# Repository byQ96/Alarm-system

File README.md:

# Alarm-system
Alarm system made under arduino platform

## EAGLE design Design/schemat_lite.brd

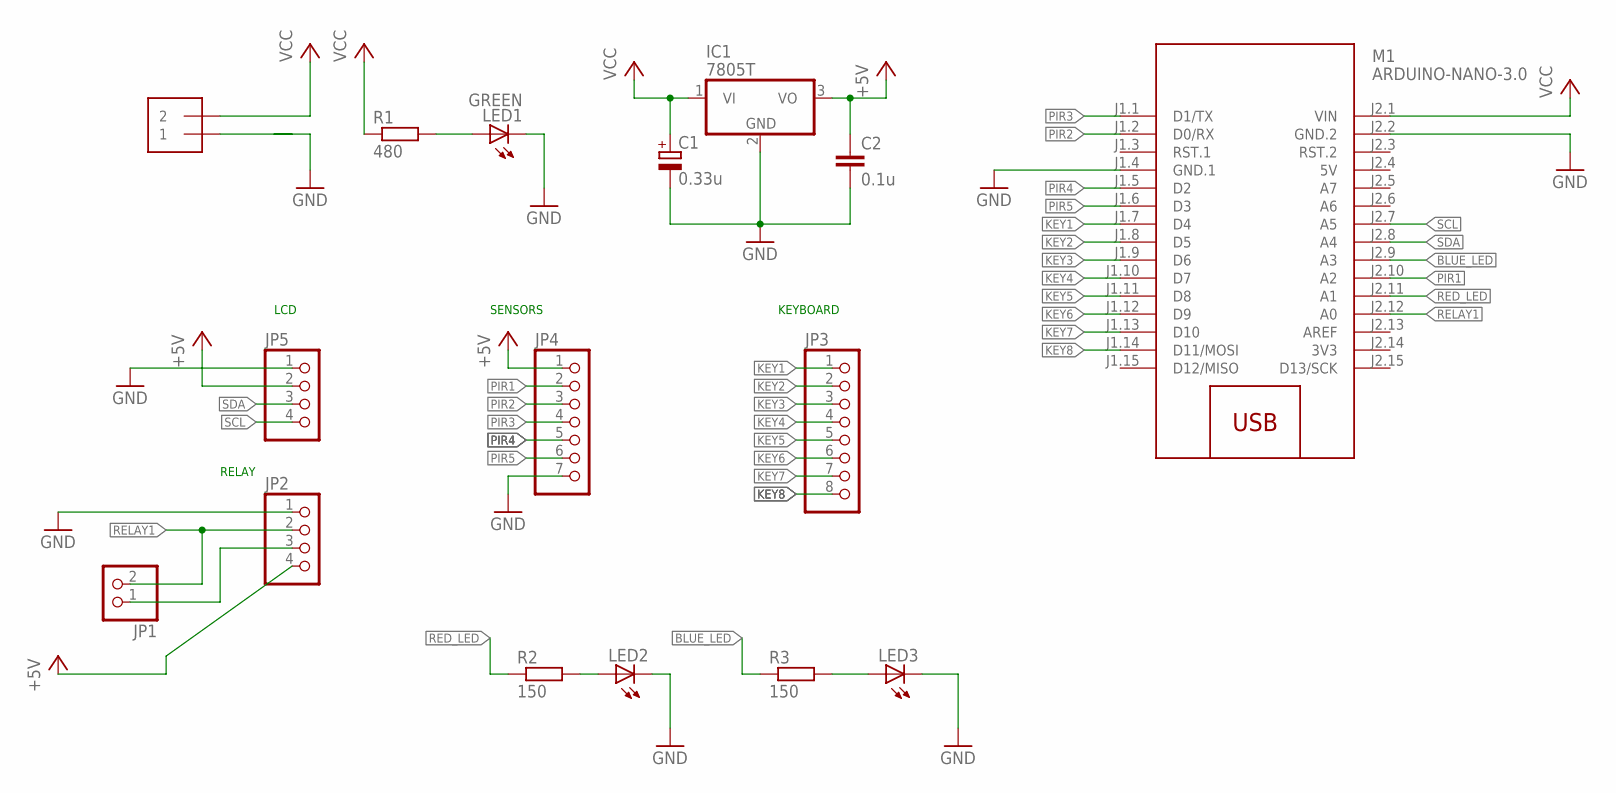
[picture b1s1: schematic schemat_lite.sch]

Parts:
C1: 0.33u; E5-4
C2: 0.1u; C050-025X075
IC1: 7805T; TO220H
J1: 1X2-3.5MM
JP1: PINHD-1X2; 1X02
JP2, JP5: PINHD-1X4; 1X04
JP3: PINHD-1X8; 1X08
JP4: PINHD-1X7; 1X07
LED1: GREEN; LED5MM
LED2, LED3: LED5MM
M1: ARDUINO-NANO-3.0
R1: 480; 0204/7
R2, R3: 150; 0204/7

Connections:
3V3: M1.J2.14 (3V3)
5V: M1.J2.4 (5V)
+5V: C2.1, IC1.3 (VO), JP2.4, JP4.1, JP5.2
BLUE_LED: M1.J2.9 (A3), R3.1
GND: C1.-, C2.2, IC1.2 (GND), J1.1, JP2.1, JP4.7, JP5.1, LED1.K (C), LED2.K (C), LED3.K (C), M1.J1.4 (GND.1), M1.J2.2 (GND.2)
KEY1: JP3.1, M1.J1.7 (D4)
KEY2: JP3.2, M1.J1.8 (D5)
KEY3: JP3.3, M1.J1.9 (D6)
KEY4: JP3.4, M1.J1.10 (D7)
KEY5: JP3.5, M1.J1.11 (D8)
KEY6: JP3.6, M1.J1.12 (D9)
KEY7: JP3.7, M1.J1.13 (D10)
KEY8: JP3.8, M1.J1.14 (D11/MOSI)
unnamed: JP1.1, JP2.3
unnamed: LED1.A, R1.2
unnamed: LED2.A, R2.2
unnamed: LED3.A, R3.2
PIR1: JP4.2, M1.J2.10 (A2)
PIR2: JP4.3, M1.J1.2 (D0/RX)
PIR3: JP4.4, M1.J1.1 (D1/TX)
PIR4: JP4.5, M1.J1.5 (D2)
PIR5: JP4.6, M1.J1.6 (D3)
RED_LED: M1.J2.11 (A1), R2.1
RELAY1: JP1.2, JP2.2, M1.J2.12 (A0)
SCL: JP5.4, M1.J2.7 (A5)
SDA: JP5.3, M1.J2.8 (A4)
VCC: C1.+, IC1.1 (VI), J1.2, M1.J2.1 (VIN), R1.1

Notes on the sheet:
LCD
RELAY
SENSORS
KEYBOARD

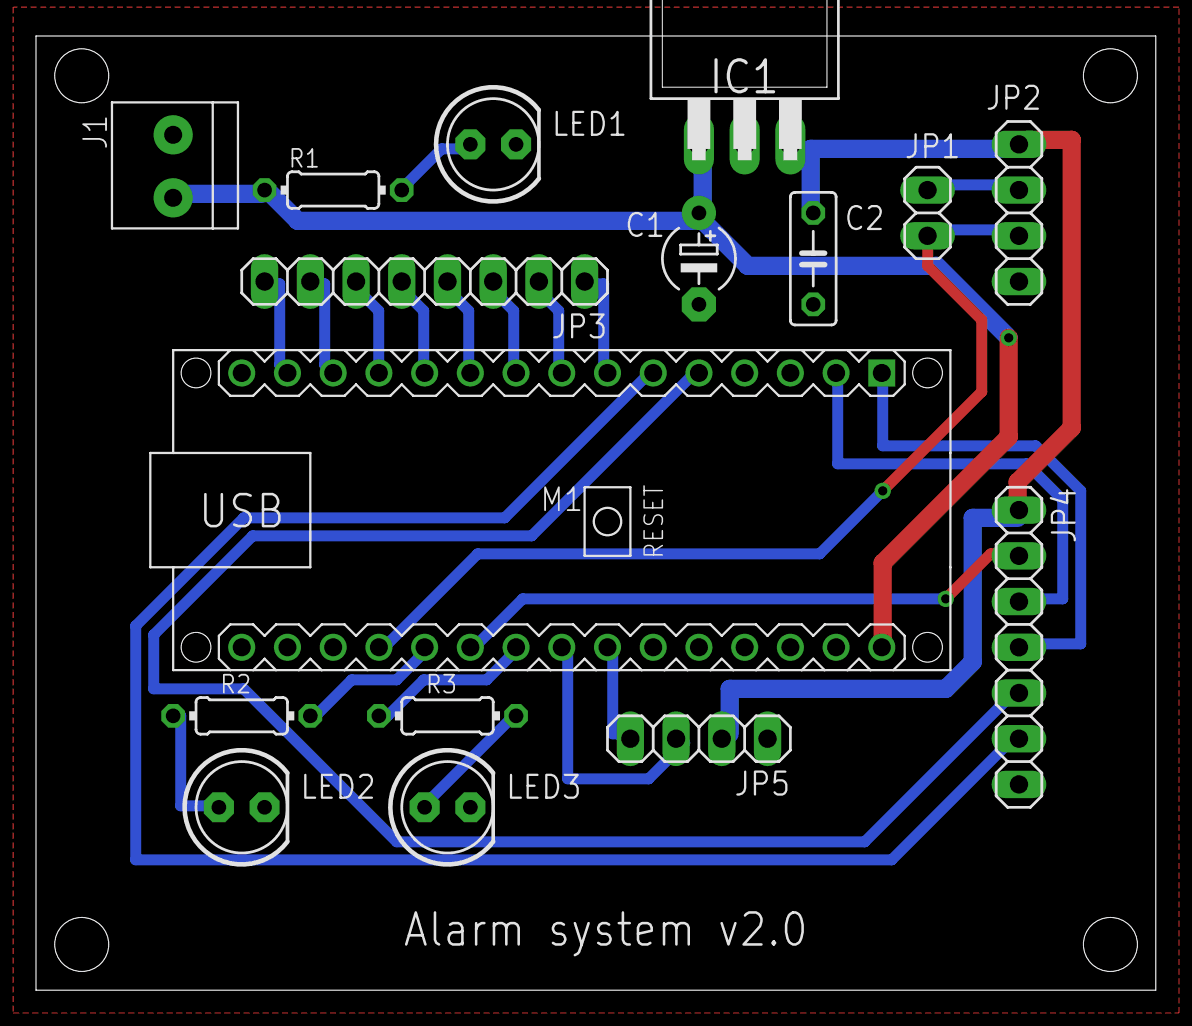
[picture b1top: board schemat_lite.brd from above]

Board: 2 copper layers, 62.2 x 53.0 mm, 16 parts (0 on the bottom side), 25 nets.

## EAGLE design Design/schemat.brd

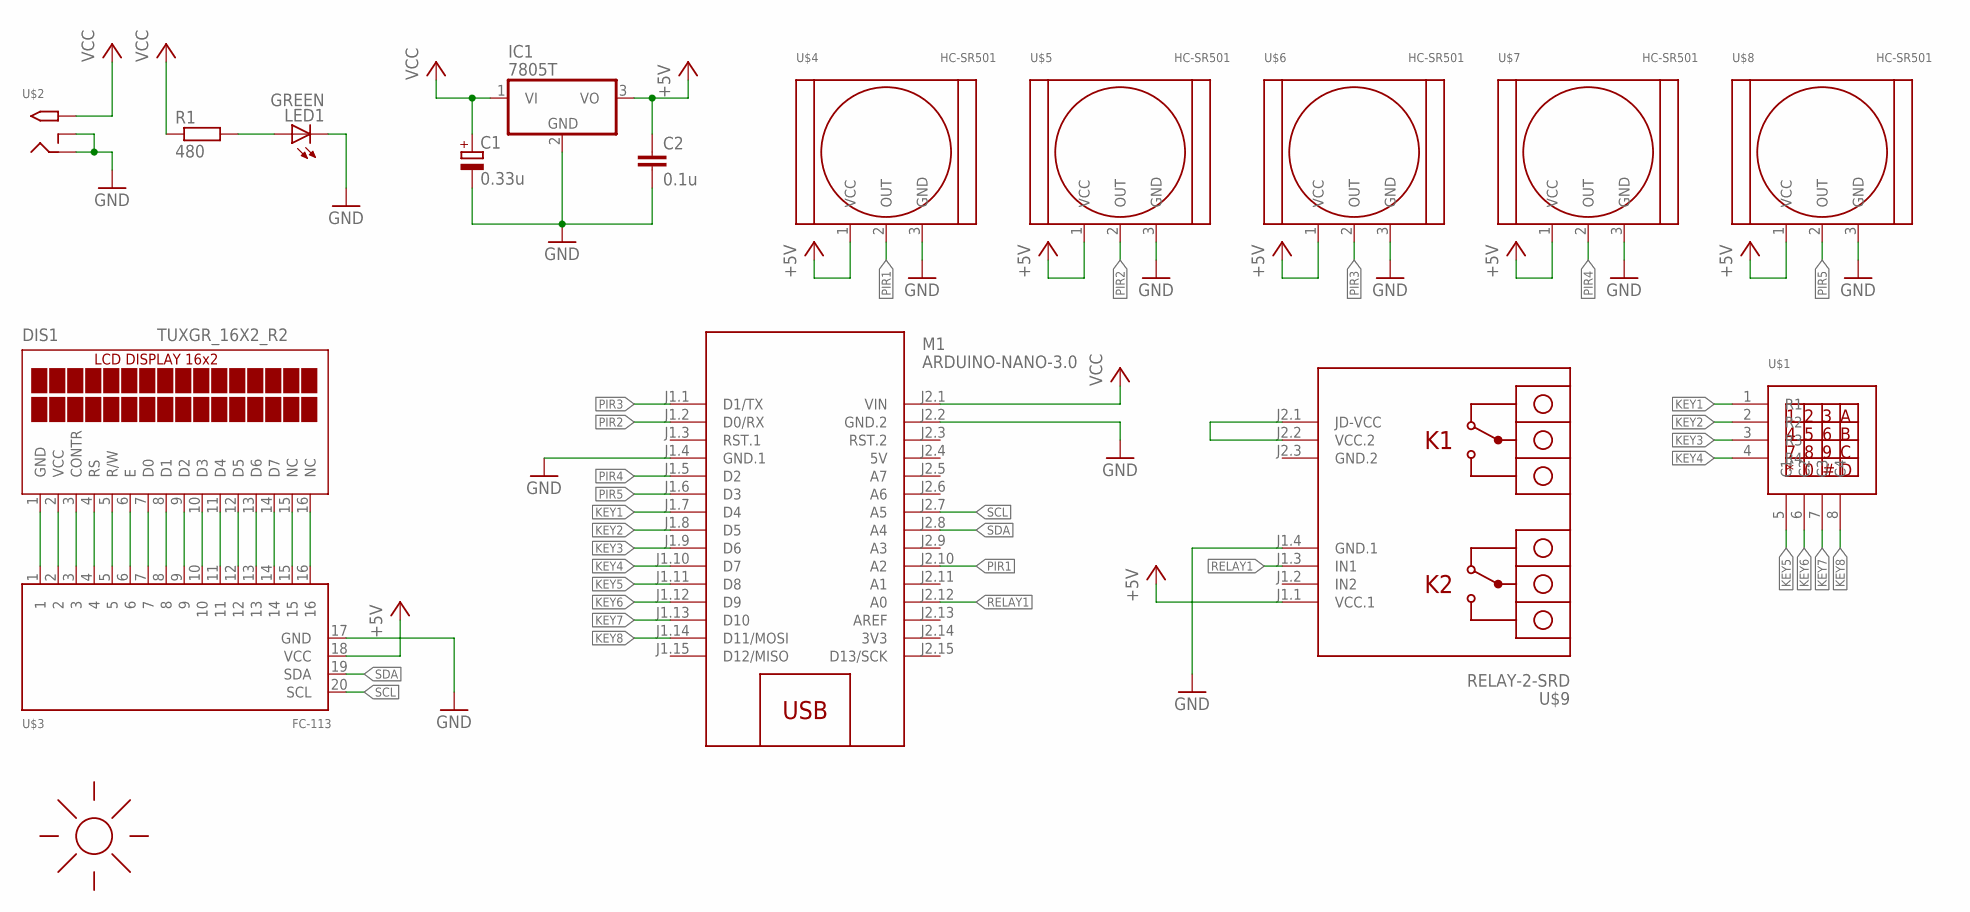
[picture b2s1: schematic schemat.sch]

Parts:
C1: 0.33u; E5-4
C2: 0.1u; C050-025X075
DIS1: TUXGR_16X2_R2
IC1: 7805T; TO220H
LED1: GREEN; LED5MM
M1: ARDUINO-NANO-3.0
R1: 480; 0204/7
U$1: KEYPAD4X4
U$2: 2.1MMJACKTHM; PJ-102A
U$3: FC-113
U$4, U$5, U$6, U$7, U$8: HC-SR501
U$9: RELAY-2-SRD
U$10: SUNLOGO; SUN

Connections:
3V3: M1.J2.14 (3V3)
5V: M1.J2.4 (5V)
+5V: C2.1, IC1.3 (VO), U$3.18 (VCC), U$4.1 (VCC), U$5.1 (VCC), U$6.1 (VCC), U$7.1 (VCC), U$8.1 (VCC), U$9.J1.1 (VCC.1)
GND: C1.-, C2.2, IC1.2 (GND), LED1.K (C), M1.J1.4 (GND.1), M1.J2.2 (GND.2), U$2.RING, U$2.RING_SW, U$3.17 (GND), U$4.3 (GND), U$5.3 (GND), U$6.3 (GND), U$7.3 (GND), U$8.3 (GND), U$9.J1.4 (GND.1)
KEY1: M1.J1.7 (D4), U$1.1 (R1)
KEY2: M1.J1.8 (D5), U$1.2 (R2)
KEY3: M1.J1.9 (D6), U$1.3 (R3)
KEY4: M1.J1.10 (D7), U$1.4 (R4)
KEY5: M1.J1.11 (D8), U$1.5 (C1)
KEY6: M1.J1.12 (D9), U$1.6 (C2)
KEY7: M1.J1.13 (D10), U$1.7 (C3)
KEY8: M1.J1.14 (D11/MOSI), U$1.8 (C4)
unnamed: DIS1.15 (NC), U$3.15
unnamed: LED1.A, R1.2
unnamed: DIS1.1 (GND), U$3.1
unnamed: DIS1.2 (VCC), U$3.2
unnamed: DIS1.3 (CONTR), U$3.3
unnamed: DIS1.4 (RS), U$3.4
unnamed: DIS1.5 (R/W), U$3.5
unnamed: DIS1.6 (E), U$3.6
unnamed: DIS1.7 (D0), U$3.7
unnamed: DIS1.8 (D1), U$3.8
unnamed: DIS1.9 (D2), U$3.9
unnamed: DIS1.10 (D3), U$3.10
unnamed: DIS1.11 (D4), U$3.11
unnamed: DIS1.12 (D5), U$3.12
unnamed: DIS1.13 (D6), U$3.13
unnamed: DIS1.14 (D7), U$3.14
unnamed: DIS1.16 (NC), U$3.16
unnamed: U$9.J2.1 (JD-VCC), U$9.J2.2 (VCC.2)
PIR1: M1.J2.10 (A2), U$4.2 (OUT)
PIR2: M1.J1.2 (D0/RX), U$5.2 (OUT)
PIR3: M1.J1.1 (D1/TX), U$6.2 (OUT)
PIR4: M1.J1.5 (D2), U$7.2 (OUT)
PIR5: M1.J1.6 (D3), U$8.2 (OUT)
RELAY1: M1.J2.12 (A0), U$9.J1.3 (IN1)
SCL: M1.J2.7 (A5), U$3.20 (SCL)
SDA: M1.J2.8 (A4), U$3.19 (SDA)
VCC: C1.+, IC1.1 (VI), M1.J2.1 (VIN), R1.1, U$2.TIP

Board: 2 copper layers, 17 parts (0 on the bottom side), 37 nets, no tracks yet.

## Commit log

2017-08-13 schemat v1
2017-08-14 schemat v2

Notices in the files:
parts and their libraries:
diy-modules: Released under the Creative Commons Attribution 4.0 International License: http://creativecommons.org/licenses/by/4.0
